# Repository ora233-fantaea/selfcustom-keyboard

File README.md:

# ESP32-S3 客制化键盘

一个基于 **Waveshare ESP32-S3-DEV-KIT-N16R8-M** 的 75% 客制化键盘工程，采用 **74HC165 级联移位寄存器**读键（非矩阵扫描），仅兼容 **Cherry MX 及兼容轴**。

> 状态：**原理图 + PCB 实质设计完成，尚未全布线**（属于可继续开发的骨架，非可投产图纸）。
> 更新日期：2026-11-23

## 特性

- **主控**：ESP32-S3-DEV-KIT-N16R8-M（16MB Flash / 8MB PSRAM），原生 USB HID。
- **读键方案**：10 片 74HC165 级联，每键独立输入 + 10kΩ 上拉，无矩阵、无二极管。
- **配列**：精确 75 键 / 6 行，方向键为标准**倒 T** 布局，Space 8.25u。
- **轴体**：75 个纯 MX 热插拔轴座（`SW_MX_HotSwap_PTH`）。
- **卫星轴**：plate-mount，4 个大键（Bksp / Enter / LShift / Space）。
- **定位板**：已建好，含键孔 / 卫星轴一体孔 / M3 孔 / 开发板避让窗，可发厂切割。
- **校验**：电气短路 **0**、走线交叉 **0**，原理图与 PCB 网络全部匹配。

## 目录结构

| 路径 | 说明 |
|---|---|
| [`kbd-esp32s3/`](kbd-esp32s3/) | KiCad 工程主体（原理图、PCB、定位板、生成脚本、预览图） |
| [`kbd-esp32s3/README.md`](kbd-esp32s3/README.md) | **工程详细文档**：电路、配列、元件、Pinout、网络、DRC、剩余边界 |
| [`ESP32-S3客制化键盘设计方案.md`](ESP32-S3客制化键盘设计方案.md) | 设计方案与选型（含主控选型、可行性结论） |
| [`ESP32-S3键盘方案_可行性验证报告.md`](ESP32-S3键盘方案_可行性验证报告.md) | 联网验证报告：GPIO / I2C / USB / PCB 设计规范 |

## 关键文件速览

- `kbd-esp32s3/kbd-esp32s3.kicad_sch` — 原理图（74HC165 级联读键）
- `kbd-esp32s3/kbd-esp32s3.kicad_pcb` — PCB（75 键 + 纯 MX 轴座 + 网络分配）
- `kbd-esp32s3/kbd-plate.dxf` — 定位板切割文件（发厂用）
- `kbd-esp32s3/pcb_preview.png` — PCB 2D 预览
- `kbd-esp32s3/render_keyboard.png` — 成品渲染图

完整的工程文件清单、电路说明、开发板 Pinout、卫星轴坐标和验证状态见 **[工程详细文档](kbd-esp32s3/README.md)**。

## 复现

工程文件由脚本生成，可在 `kbd-esp32s3/` 下重跑（需要 KiCad 9 的 `pcbnew` Python 模块）：

```bash
cd kbd-esp32s3
python3 gen_sch.py          # 原理图
python3 gen_pcb.py          # PCB（会覆盖 .kicad_pcb）
python3 gen_stabilizers.py  # 卫星轴开孔坐标表 + 示意图
python3 gen_plate.py        # 定位板 + DXF
python3 render_keyboard.py  # 成品渲染图
```

## 下一步

- 在 KiCad GUI 中完成 **397 条飞线**的布线（按键扫描线 / 电源 / 时钟 / 编码器 / USB）。
- 补副屏（SPI 长条屏）接口、外壳配合、实物焊接验证。
- 详情见 [工程详细文档 · 剩余边界](kbd-esp32s3/README.md#剩余边界下一步)。

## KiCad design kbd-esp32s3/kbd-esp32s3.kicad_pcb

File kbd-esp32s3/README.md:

# ESP32-S3 客制化键盘 · KiCad 工程

> 更新日期：2026-11-23
> 状态：**原理图 + PCB 实质设计**（非可投产图纸，布线未完成）
> 主控：Waveshare ESP32-S3-DEV-KIT-N16R8-M（16MB Flash / 8MB PSRAM）
> 轴体：**仅 Cherry MX 及兼容轴（已放弃 MX/Choc 混合兼容）**

## 工程文件

| 文件 | 说明 |
|---|---|
| `kbd-esp32s3.kicad_pro` | KiCad 9 工程文件 |
| `kbd-esp32s3.kicad_sch` | 原理图：74HC165 级联读键电路（非矩阵） |
| `kbd-esp32s3.kicad_pcb` | PCB：75 键真实配列 + 纯 MX 热插拔轴座 + 完整网络分配 |
| `gen_sch.py` / `lib_extract.py` | 原理图生成脚本（符号提取 + 布局 + 标签） |
| `gen_pcb.py` | PCB 生成脚本（pcbnew API，可重跑：配列/封装/网络/级联布线） |
| `gen_stabilizers.py` | 卫星轴定位板开孔数据生成（坐标表 + 示意图，可重跑） |
| `stabilizer_plate_holes.md` | 卫星轴开孔坐标表 + 采购清单 |
| `stabilizer_layout.png` | 卫星轴孔位示意图 |
| `gen_plate.py` | 定位板生成脚本（可重跑） |
| `kbd-plate.kicad_pcb` | 定位板板文件（Edge.Cuts：板框/键孔/卫星孔/M3/避让窗） |
| `kbd-plate.dxf` | 定位板切割文件（Edge.Cuts 层，发厂激光切割/CNC） |
| `plate_preview.png` | 定位板预览图 |

## 键盘输入电路（原理图和 PCB 一致）

**方案：74HC165 级联，每键独立输入，无矩阵、无二极管。**

- 10 片 74HC165，每片 8 路并行输入 = 80 路，覆盖 75 键，5 路空余接地。
- 每键：轴座 + 10kΩ 上拉电阻，独立接入一片 74HC165 的输入。
- 级联：前级 `Q7`(pin9) → 后级 `DS`(pin10)，网络 `CHAIN_1..CHAIN_9`；末片 `Q7` → `DATA`。
- 并行时钟 `CLK`(pin2)、锁存 `SH_LD`(pin1, 低有效) 全局并联；`~CE`(pin15) 接地常使能。
- 编码器：EC11 带按压，`ENC_A/ENC_B/ENC_SW` 独立引出，不进级联链。
- 接口：ESP32 开发板插座 = 两条独立 **1×22** 排母（P1/P2，2.54mm 间距），**两排中心距 21.80mm**；
  针数与中心距均按官方机械图 `ESP32-S3-DEV-KIT-N8R8_20260110` 与原理图 `Header 22` 标注核对，详见 `MODULE_CHECK.md`。
  板载 USB-C（J_USB）仅作原生 USB 数据备用，VBUS 不接。

## PCB 设计（本次完成）

### 配列：精确 75 键 / 6 行

| 行 | 键数 | 内容 |
|---|---|---|
| Row0 功能行 | 13 | Esc + F1~F12 |
| Row1 数字行 | 14 | ` 1-0 - = + Bksp(2u) |
| Row2 Q 行 | 14 | Tab(1.5u) Q-P [ ] \(1.5u) |
| Row3 A 行 | 13 | Caps(1.75u) A-L ; ' + Enter(2.25u) |
| Row4 Z 行 | 13 | LShift(2.25u) Z-M , . / + RShift(1.75u) + ↑ |
| Row5 底行 | 8 | LCtrl LWin LAlt + Space(8.25u) + Fn ← ↓ → |

- 键距 19.05mm，宽键按单位 u 计算，板框 **337.8 × 164.3mm**（重做后收紧：顶部窄带放开发板排针，74HC165 芯片带紧贴键区下方，消除了原底部约 60mm 空白）。
- **方向键采用标准倒 T 布局**：↑ 中心与 ↓ 对齐（x=14.5u），← ↓ → 三键并排在底行右侧，整簇紧凑、符合常规使用习惯。为腾出倒 T 所需空间，RShift 由 2.75u 缩至 1.75u、Space 由 6.25u 加长至 8.25u，总键数仍为 75。

### 元件

| 元件 | 数量 | 封装 / 说明 |
|---|---|---|
| 纯 MX 热插拔轴座 | 75 | `SW_MX_HotSwap_PTH`（仅 Cherry MX 及兼容轴，pad1=信号 / pad2=GND） |
| 上拉电阻 10k | 75 | 0603，pad1→VCC，pad2→按键网络 |
| 74HC165 | 10 | SOIC-16W，贴近对应键位组 |
| 去耦电容 100nF | 10 | 0603，每片 74HC165 一个 |
| ESP32 开发板插座 | 2 | 各 **1×22** 排母（P1/P2，2.54mm），水平放置，**中心距 21.80mm**，首针距板端 5.05/4.91mm；模块本体 63.30×25.40，四角 Ø2 安装孔（M1.4） |
| EC11 编码器 | 1 | 带按压开关 |
| USB-C | 1 | GCT USB4085（预留接口） |
| 安装孔 M3 | 4 | 四角 |

### 防共振开槽（Edge.Cuts 铣槽）

板面开槽用于打散整块 PCB 的弯曲共振、降低空腔音。**全部槽在 Edge.Cuts 层画闭合矩形**，74 个闭合轮廓（1 板框 + 73 槽）已验证全部闭合，KiCad/厂家按板内挖空（锣槽）处理。

- **大键减振槽**（5 处）：Space(8.25u) / Bksp(2u) / Enter(2.25u) / LShift(2.25u) / 底行右侧大键，在键中心上方 y=cy−8 开一条长槽（Space 槽长 152mm），打断大键下方整片板面的共振。槽宽 1.2mm。
- **键位隔离槽**（每键右上）：相邻键之间开竖槽，只开键的上半段（y 从 cy−6.5 到 cy−8），**下端留桥不贯穿**——MX 轴座焊盘集中在下半（y=+2.54/+5.08），槽避开焊盘区，同时保留机械连接不让板子散架。
- 槽位置经过 DRC 校验：`copper_edge_clearance` = **0**（不切焊盘/走线），短路 0、走线交叉 0。
- 可视化：`render_slots.py` 从 PCB 真实坐标生成 `pcb_slots_annotated.png`（红=槽）。

### 卫星轴（plate-mount，定位板卡扣）

**结论：卫星轴装在定位板上，PCB 无需开孔、无需改板。** 之前 PCB 未体现属正常，但定位板开孔坐标与 BOM 此前缺失，现已补齐（见 `gen_stabilizers.py` / `stabilizer_plate_holes.md` / `stabilizer_layout.png`）。

- 覆盖范围：**仅 2u 以上**（Bksp 2u / Enter 2.25u / LShift 2.25u / Space 8.25u），共 4 键 8 个 housing 位。
- 开孔：每个 housing 位约 6.65×12.3mm 矩形，中心坐标见 `stabilizer_plate_holes.md`（与 KiCad 板坐标一致）。
- 采购：2u plate-mount ×3、8u plate-mount ×1（2u/2.25u/2.75u 共用同一 2u 卫星轴）。
- **坑**：Space 是 8.25u，Cherry 无此档位；已按用户确认的 **8u（孔距 133.35mm，X=108.34/241.69）** 定死，下单键帽前仍须实测其卫星轴孔距。详见坐标表注意事项。

**定位板已建**（`gen_plate.py` 生成，**专为 MX 轴设计**）：整块 337.8×164.3mm（与重做后 PCB 一致），键孔 14×14（MX 标准）；2u/2.25u 大键的轴孔与卫星孔用 5mm 窄颈连通成一体开孔（plate-mount housing 必须这样才卡得进去），空格因卫星孔距中心 66.675mm 保持三孔独立。输出 `kbd-plate.kicad_pcb`（KiCad 可打开）与 `kbd-plate.dxf`（发厂切割）。避让窗 x[140,198] y[2,31] 供开发板排针。

### 开发板插座 Pinout（依据微雪官方原理图/尺寸图）

数据来源：[Waveshare ESP32-S3-DEV-KIT 文档](https://docs.waveshare.com/ESP32-S3-DEV-KIT-N8R8)、官方机械图包（PDF/DXF/STEP）、官方原理图。
实测标注：板体 63.30 × 25.40mm，2×22 排针 @2.54mm，两排中心距 21.80mm，排针距板边 1.80mm。
> 注：21.80mm 不是 2.54 的整数倍，因此该模块无法插入标准面包板——这是模块本身的特性。

| P1 (J_P1) | 网络 | P2 (J_P2) | 网络 |
|---|---|---|---|
| 1 | 3V3 → VCC | 1 | GND |
| 2 | EN → NC | 2 | TXD / GPIO43 |
| 3 | GPIO4 → **CLK** | 3 | RXD / GPIO44 |
| 4 | GPIO5 → **SH_LD** | 4 | GPIO1 |
| 5 | GPIO6 → **DATA** | 5 | GPIO2 |
| 6 | GPIO7 → **ENC_A** | 6 | GPIO42 |
| 7 | GPIO15 → **ENC_B** | 7 | GPIO41 |
| 8 | GPIO16 → **ENC_SW** | 8 | GPIO40 |
| 9 | GPIO17 | 9 | GPIO39 |
| 10 | GPIO18 | 10 | GPIO38 |
| 11 | GPIO8 | 11 | GPIO37 |
| 12 | GPIO3 | 12 | GPIO36 |
| 13 | GPIO46 | 13 | GPIO35 |
| 14 | GPIO9 | 14 | GPIO0 (BOOT) |
| 15 | GPIO10 | 15 | GPIO45 |
| 16 | GPIO11 | 16 | GPIO48 |
| 17 | GPIO12 | 17 | GPIO47 |
| 18 | GPIO13 | 18 | GPIO21 |
| 19 | GPIO14 | 19 | GPIO20 (USB D+) |
| 20 | 5V → NC | 20 | GPIO19 (USB D-) |

> 注：本项目需要的 6 个信号（CLK/SH_LD/DATA/ENC_A/B/SW）已映射到 P1 的 GPIO4/5/6/7/15/16；其余 GPIO 针脚按官方定义保留网络名备用。NC 引脚为板子上未连接/NC 的 GPIO（如 GPIO35/36/37 在 WROOM-1 上不引出）。

### 网络分配

- 129 个网络：K01~K75（按键）、CHAIN_1~10（级联，末片 CHAIN_10 即 ESP32 DATA）、CLK、SH_LD、ENC_A/B/SW、GPIO1~48（开发板插座备用针脚）、VCC、GND、VBUS、USB_D±、CC1/CC2。
- 原理图 92 个网络与 PCB **全部匹配**（已脚本核对），GUI 中 F8 同步不会报网络错误。
- **所有焊盘已分配网络**（网络名即飞线依据）。
- 已预布最关键的**级联数据链**：Q7/DS 为 SOIC 相邻引脚，同层无法避开交叉，故级联改走 **B.Cu 背面独立通道**（出口列打过孔下到背面），正面所有引线零交叉。

## 验证状态

| 检查项 | 结果 |
|---|---|
| 原理图加载 / ERC 电气错误 | ✅ 通过 / 0 error |
| PCB 加载 / 导出 SVG | ✅ 通过 |
| DRC 电气短路（shorting_items） | ✅ **0 个** |
| DRC 未连接项 | 397（预期：按键扫描线/电源/时钟/地尚未布线） |
| 其余 DRC 警告 | 240 项非电气警告：courtyard_overlap 75 + hole_clearance 151（轴座 PTH 孔密集的固有特性）+ clearance 14（USB-C 密脚封装固有 0.15mm 间隙）。短路 0、走线交叉 0。 |

## 剩余边界（下一步）

1. **布线未完成**：397 个飞线需在 KiCad GUI 中完成（自动布线器或手动）——按键扫描线、上拉电阻 VCC、74HC165 电源/时钟/锁存、编码器、USB。级联数据链已预布（走 B.Cu）。
2. **网表同步**：本 PCB 的网络分配由脚本直接写入，与原理图网络名一致；GUI 打开后可执行 F8 核对。
3. **ERC 10 个 `lib_symbol_mismatch`**：74HC165 继承符号展开的缓存差异，"更新符号库缓存"可消除，非电气问题。
4. **DRC 布局警告**：240 项均为机械/密脚警告（轴座 PTH 孔间距、USB-C 密脚），非短路非交叉；可后续调整孔间距规则清理，不影响电气。
5. **尚未做**：副屏（SPI 长条屏）接口、真实外壳/定位板配合、MX 轴座的实物焊接验证。级联链已改走 B.Cu 背面独立通道，消除了 F.Cu 相邻引脚跨接交叉。
6. **定位板**：已建好（`kbd-plate.kicad_pcb` + `kbd-plate.dxf`），板框 337.8×164.3mm、与 PCB 对齐；含 75 个 14×14 键孔、8 个卫星轴孔（2u 级与中心轴孔用窄颈连通为一体孔，空格三孔独立）、4×M3 Ø3.2、顶部开发板避让窗。建议 1.5mm FR4 或铝板，发厂用 `kbd-plate.dxf`。PCB 无需改动。

## 环境说明

- KiCad 9.0.9（官方 PPA）；headless 环境，用 `kicad-cli` 和 `pcbnew` Python API 操作。
- 第三方键盘封装库：`/root/.local/share/kicad/9.0/footprints/`。
- 全局库表 `sym-lib-table` / `fp-lib-table` 已配置在 `~/.config/kicad/9.0/`。
- 重跑生成：`python3 gen_pcb.py`（会覆盖 .kicad_pcb）。

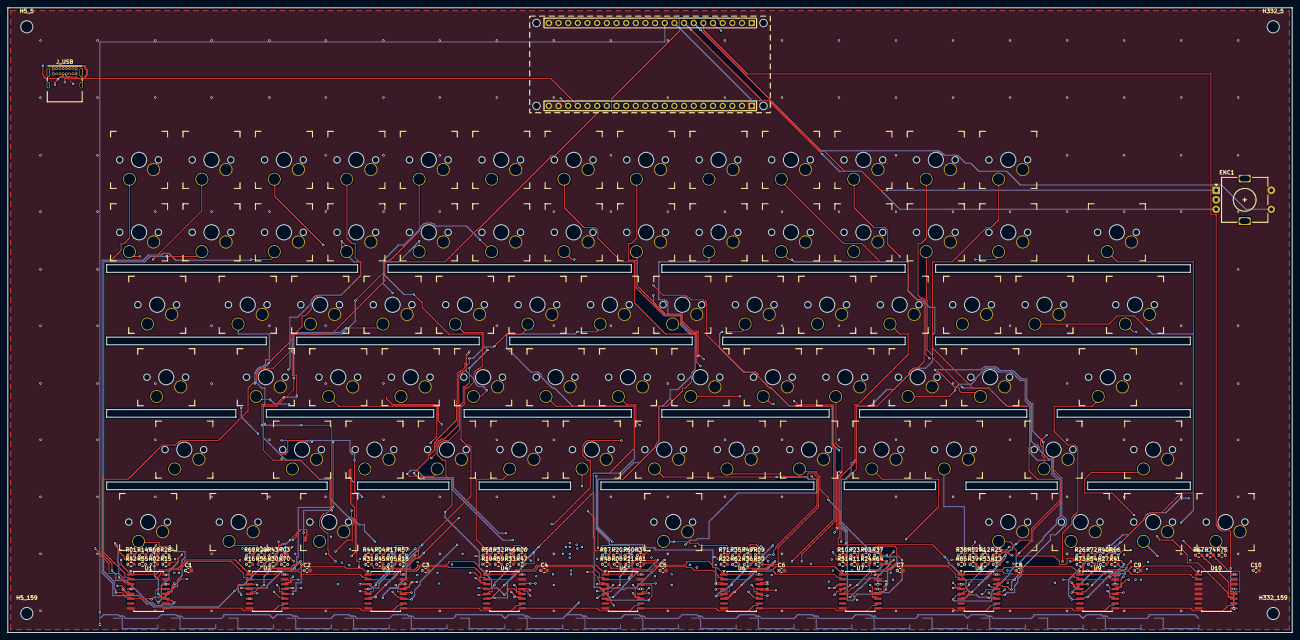
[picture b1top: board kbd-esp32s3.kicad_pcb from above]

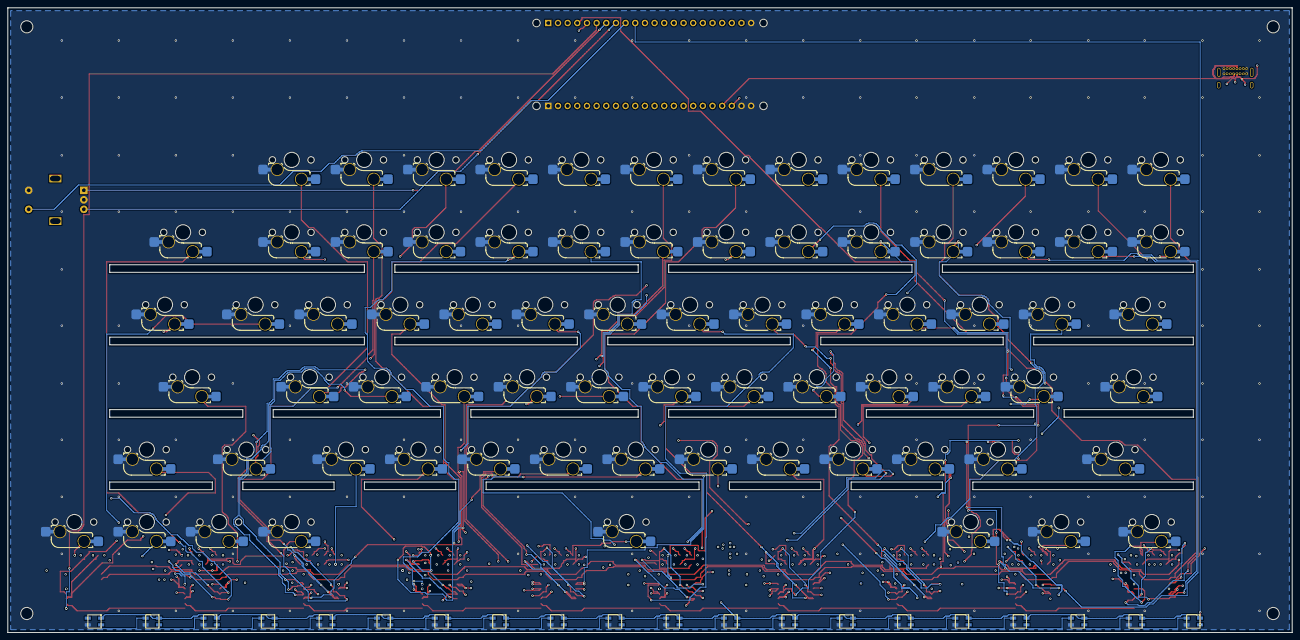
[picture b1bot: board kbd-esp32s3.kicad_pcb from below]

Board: 4 copper layers, 337.8 x 164.3 mm, 199 parts (20 on the bottom side), 115 nets.

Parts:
C1, C2, C3, C4, C5, C6, C7, C8, C9, C10: 100nF; C_0603_1608Metric
ENC1: EC11; RotaryEncoder_Alps_EC11E-Switch_Vertical_H20mm
H5_5, H5_159, H332_5, H332_159: M3; MountingHole_3.2mm_M3
J_P1: DEV-KIT-P1; PinHeader_1x22_P2.54mm_Vertical
J_P2: DEV-KIT-P2; PinHeader_1x22_P2.54mm_Vertical
J_USB: USB-C(数据备用); USB_C_Receptacle_GCT_USB4085
L01, L02, L03, L04, L05, L06, L07, L08, L09, L10, L11, L12, L13, L14, L15, L16, L17, L18, L19, L20: SK6812MINI-E; LED_SK6812MINI-E
MOD1: ESP32-S3-DEV-KIT-N16R8-M; Waveshare_ESP32-S3-DEV-KIT-N16R8-M
R01, R02, R03, R04, R05, R06, R07, R08, R09, R10, R11, R12, R13, R14, R15, R16, R17, R18, R19, R20, R21, R22, R23, R24, R25, R26, R27, R28, R29, R30, R31, R32, R33, R34, R35, R36, R37, R38, R39, R40, R41, R42, R43, R44, R45, R46, R47, R48, R49, R50, R51, R52, R53, R54, R55, R56, R57, R58, R59, R60, R61, R62, R63, R64, R65, R66, R67, R68, R69, R70, R71, R72, R73, R74, R75: 10k; R_0603_1608Metric
SW01: Esc; SW_MX_HotSwap_PTH
SW02: F1; SW_MX_HotSwap_PTH
SW03: F2; SW_MX_HotSwap_PTH
SW04: F3; SW_MX_HotSwap_PTH
SW05: F4; SW_MX_HotSwap_PTH
SW06: F5; SW_MX_HotSwap_PTH
SW07: F6; SW_MX_HotSwap_PTH
SW08: F7; SW_MX_HotSwap_PTH
SW09: F8; SW_MX_HotSwap_PTH
SW10: F9; SW_MX_HotSwap_PTH
SW11: F10; SW_MX_HotSwap_PTH
SW12: F11; SW_MX_HotSwap_PTH
SW13: F12; SW_MX_HotSwap_PTH
SW14: `; SW_MX_HotSwap_PTH
SW15: 1; SW_MX_HotSwap_PTH
SW16: 2; SW_MX_HotSwap_PTH
SW17: 3; SW_MX_HotSwap_PTH
SW18: 4; SW_MX_HotSwap_PTH
SW19: 5; SW_MX_HotSwap_PTH
SW20: 6; SW_MX_HotSwap_PTH
SW21: 7; SW_MX_HotSwap_PTH
SW22: 8; SW_MX_HotSwap_PTH
SW23: 9; SW_MX_HotSwap_PTH
SW24: 0; SW_MX_HotSwap_PTH
SW25: -; SW_MX_HotSwap_PTH
SW26: =; SW_MX_HotSwap_PTH
SW27: Bksp; SW_MX_HotSwap_PTH
SW28: Tab; SW_MX_HotSwap_PTH
SW29: Q; SW_MX_HotSwap_PTH
SW30: W; SW_MX_HotSwap_PTH
SW31: E; SW_MX_HotSwap_PTH
SW32: R; SW_MX_HotSwap_PTH
SW33: T; SW_MX_HotSwap_PTH
SW34: Y; SW_MX_HotSwap_PTH
SW35: U; SW_MX_HotSwap_PTH
SW36: I; SW_MX_HotSwap_PTH
SW37: O; SW_MX_HotSwap_PTH
SW38: P; SW_MX_HotSwap_PTH
SW39: [; SW_MX_HotSwap_PTH
SW40: ]; SW_MX_HotSwap_PTH
SW41: \\\\\\\\\\\\\\\\\\\\\\\\\\\\\\\\\\\\\\\\\\\\\\\\\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; SW_MX_HotSwap_PTH
SW42: Caps; SW_MX_HotSwap_PTH
SW43: A; SW_MX_HotSwap_PTH
SW44: S; SW_MX_HotSwap_PTH
SW45: D; SW_MX_HotSwap_PTH
SW46: F; SW_MX_HotSwap_PTH
SW47: G; SW_MX_HotSwap_PTH
SW48: H; SW_MX_HotSwap_PTH
SW49: J; SW_MX_HotSwap_PTH
SW50: K; SW_MX_HotSwap_PTH
SW51: L; SW_MX_HotSwap_PTH
SW52: ;; SW_MX_HotSwap_PTH
SW53: '; SW_MX_HotSwap_PTH
SW54: Enter; SW_MX_HotSwap_PTH
SW55: LShift; SW_MX_HotSwap_PTH
SW56: Z; SW_MX_HotSwap_PTH
SW57: X; SW_MX_HotSwap_PTH
SW58: C; SW_MX_HotSwap_PTH
SW59: V; SW_MX_HotSwap_PTH
SW60: B; SW_MX_HotSwap_PTH
SW61: N; SW_MX_HotSwap_PTH
SW62: M; SW_MX_HotSwap_PTH
SW63: ,; SW_MX_HotSwap_PTH
SW64: .; SW_MX_HotSwap_PTH
SW65: /; SW_MX_HotSwap_PTH
SW66: RShift; SW_MX_HotSwap_PTH
SW67: Up; SW_MX_HotSwap_PTH
SW68: LCtrl; SW_MX_HotSwap_PTH
SW69: LWin; SW_MX_HotSwap_PTH
SW70: LAlt; SW_MX_HotSwap_PTH
SW71: Space; SW_MX_HotSwap_PTH
SW72: Fn; SW_MX_HotSwap_PTH
SW73: Left; SW_MX_HotSwap_PTH
SW74: Down; SW_MX_HotSwap_PTH
SW75: Right; SW_MX_HotSwap_PTH
U1, U2, U3, U4, U5, U6, U7, U8, U9, U10: 74HC165; SOIC-16W_7.5x10.3mm_P1.27mm

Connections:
CHAIN_1: U1.9, U2.10
CHAIN_2: U2.9, U3.10
CHAIN_3: U3.9, U4.10
CHAIN_4: U4.9, U5.10
CHAIN_5: U5.9, U6.10
CHAIN_6: U6.9, U7.10
CHAIN_7: U7.9, U8.10
CHAIN_8: U8.9, U9.10
CHAIN_9: U9.9, U10.10
CHAIN_10: J_P1.6, U10.9
CLK: J_P1.4, U1.2, U2.2, U3.2, U4.2, U5.2, U6.2, U7.2, U8.2, U9.2, U10.2
ENC_A: ENC1.A, J_P1.7
ENC_B: ENC1.B, J_P1.8
ENC_SW: ENC1.S1, J_P1.9
GND: C1.2, C2.2, C3.2, C4.2, C5.2, C6.2, C7.2, C8.2, C9.2, C10.2, ENC1.C, ENC1.S2, J_P1.22, J_P2.1, J_P2.21, J_P2.22, J_USB.A1, J_USB.A12, J_USB.B1, J_USB.B12, L01.3, L02.3, L03.3, L04.3, L05.3, L06.3, L07.3, L08.3, L09.3, L10.3, L11.3, L12.3, L13.3, L14.3, L15.3, L16.3, L17.3, L18.3, L19.3, L20.3, SW01.2, SW02.2, SW03.2, SW04.2, SW05.2, SW06.2, SW07.2, SW08.2, SW09.2, SW10.2, SW11.2, SW12.2, SW13.2, SW14.2, SW15.2, SW16.2, SW17.2, SW18.2, SW19.2, SW20.2, SW21.2, SW22.2, SW23.2, SW24.2, SW25.2, SW26.2, SW27.2, SW28.2, SW29.2, SW30.2, SW31.2, SW32.2, SW33.2, SW34.2, SW35.2, SW36.2, SW37.2, SW38.2, SW39.2, SW40.2, SW41.2, SW42.2, SW43.2, SW44.2, SW45.2, SW46.2, SW47.2, SW48.2, SW49.2, SW50.2, SW51.2, SW52.2, SW53.2, SW54.2, SW55.2, SW56.2, SW57.2, SW58.2, SW59.2, SW60.2, SW61.2, SW62.2, SW63.2, SW64.2, SW65.2, SW66.2, SW67.2, SW68.2, SW69.2, SW70.2, SW71.2, SW72.2, SW73.2, SW74.2, SW75.2, U1.8, U1.10, U1.15, U2.8, U2.15, U3.8, U3.15, U4.8, U4.15, U5.8, U5.15, U6.8, U6.15, U7.8, U7.15, U8.8, U8.15, U9.8, U9.15, U10.3, U10.4, U10.5, U10.6, U10.8, U10.14, U10.15
K01: R01.2, SW01.1, U1.11
K02: R02.2, SW02.1, U1.5
K03: R03.2, SW03.1, U2.14
K04: R04.2, SW04.1, U3.12
K05: R05.2, SW05.1, U3.5
K06: R06.2, SW06.1, U4.14
K07: R07.2, SW07.1, U5.11
K08: R08.2, SW08.1, U5.4
K09: R09.2, SW09.1, U6.14
K10: R10.2, SW10.1, U7.11
K11: R11.2, SW11.1, U7.4
K12: R12.2, SW12.1, U8.13
K13: R13.2, SW13.1, U8.6
K14: R14.2, SW14.1, U1.12
K15: R15.2, SW15.1, U1.6
K16: R16.2, SW16.1, U2.3
K17: R17.2, SW17.1, U3.13
K18: R18.2, SW18.1, U3.6
K19: R19.2, SW19.1, U4.3
K20: R20.2, SW20.1, U5.12
K21: R21.2, SW21.1, U5.5
K22: R22.2, SW22.1, U6.3
K23: R23.2, SW23.1, U7.12
K24: R24.2, SW24.1, U7.5
K25: R25.2, SW25.1, U8.14
K26: R26.2, SW26.1, U9.11
K27: R27.2, SW27.1, U9.5
K28: R28.2, SW28.1, U1.14
K29: R29.2, SW29.1, U2.12
K30: R30.2, SW30.1, U2.5
K31: R31.2, SW31.1, U3.3
K32: R32.2, SW32.1, U4.12
K33: R33.2, SW33.1, U4.5
K34: R34.2, SW34.1, U5.14
K35: R35.2, SW35.1, U6.12
K36: R36.2, SW36.1, U6.5
K37: R37.2, SW37.1, U7.14
K38: R38.2, SW38.1, U8.11
K39: R39.2, SW39.1, U8.4
K40: R40.2, SW40.1, U9.13
K41: R41.2, SW41.1, U9.6
K42: R42.2, SW42.1, U1.3
K43: R43.2, SW43.1, U2.13
K44: R44.2, SW44.1, U3.11
K45: R45.2, SW45.1, U3.4
K46: R46.2, SW46.1, U4.13
K47: R47.2, SW47.1, U4.6
K48: R48.2, SW48.1, U5.3
K49: R49.2, SW49.1, U6.13
K50: R50.2, SW50.1, U6.6
K51: R51.2, SW51.1, U7.3
K52: R52.2, SW52.1, U8.12
K53: R53.2, SW53.1, U8.5
K54: R54.2, SW54.1, U9.4
K55: R55.2, SW55.1, U1.4
K56: R56.2, SW56.1, U2.4
K57: R57.2, SW57.1, U3.14
K58: R58.2, SW58.1, U4.11
K59: R59.2, SW59.1, U4.4
K60: R60.2, SW60.1, U5.13
K61: R61.2, SW61.1, U5.6
K62: R62.2, SW62.1, U6.4
K63: R63.2, SW63.1, U7.13
K64: R64.2, SW64.1, U7.6
K65: R65.2, SW65.1, U8.3
K66: R66.2, SW66.1, U9.14
K67: R67.2, SW67.1, U10.11
K68: R68.2, SW68.1, U1.13
K69: R69.2, SW69.1, U2.11
K70: R70.2, SW70.1, U2.6
K71: R71.2, SW71.1, U6.11
K72: R72.2, SW72.1, U9.12
K73: R73.2, SW73.1, U9.3
K74: R74.2, SW74.1, U10.12
K75: R75.2, SW75.1, U10.13
LED_D0: L01.2, L02.4
LED_D1: L02.2, L03.4
LED_D2: L03.2, L04.4
LED_D3: L04.2, L05.4
LED_D4: L05.2, L06.4
LED_D5: L06.2, L07.4
LED_D6: L07.2, L08.4
LED_D7: L08.2, L09.4
LED_D8: L09.2, L10.4
LED_D9: L10.2, L11.4
LED_D10: L11.2, L12.4
LED_D11: L12.2, L13.4
LED_D12: L13.2, L14.4
LED_D13: L14.2, L15.4
LED_D14: L15.2, L16.4
LED_D15: L16.2, L17.4
LED_D16: L17.2, L18.4
LED_D17: L18.2, L19.4
LED_D18: L19.2, L20.4
LED_DATA: J_P1.10, L01.4
SH_LD: J_P1.5, U1.1, U2.1, U3.1, U4.1, U5.1, U6.1, U7.1, U8.1, U9.1, U10.1
USB_D+: J_P2.19, J_USB.A6, J_USB.B6
USB_D-: J_P2.20, J_USB.A7, J_USB.B7
V5: J_P1.21, L01.1, L02.1, L03.1, L04.1, L05.1, L06.1, L07.1, L08.1, L09.1, L10.1, L11.1, L12.1, L13.1, L14.1, L15.1, L16.1, L17.1, L18.1, L19.1, L20.1
VCC: C1.1, C2.1, C3.1, C4.1, C5.1, C6.1, C7.1, C8.1, C9.1, C10.1, J_P1.1, J_P1.2, R01.1, R02.1, R03.1, R04.1, R05.1, R06.1, R07.1, R08.1, R09.1, R10.1, R11.1, R12.1, R13.1, R14.1, R15.1, R16.1, R17.1, R18.1, R19.1, R20.1, R21.1, R22.1, R23.1, R24.1, R25.1, R26.1, R27.1, R28.1, R29.1, R30.1, R31.1, R32.1, R33.1, R34.1, R35.1, R36.1, R37.1, R38.1, R39.1, R40.1, R41.1, R42.1, R43.1, R44.1, R45.1, R46.1, R47.1, R48.1, R49.1, R50.1, R51.1, R52.1, R53.1, R54.1, R55.1, R56.1, R57.1, R58.1, R59.1, R60.1, R61.1, R62.1, R63.1, R64.1, R65.1, R66.1, R67.1, R68.1, R69.1, R70.1, R71.1, R72.1, R73.1, R74.1, R75.1, U1.16, U2.16, U3.16, U4.16, U5.16, U6.16, U7.16, U8.16, U9.16, U10.16

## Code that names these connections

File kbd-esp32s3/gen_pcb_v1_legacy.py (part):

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             nets=p2_nets, rot=90)

# 项目信号 -> 开发板 GPIO（用标签网络名保持一致，便于飞线）
# CLK->GPIO4(P1.3), SH_LD->GPIO5(P1.4), CHAIN_10(DATA)->GPIO6(P1.5)
# ENC_A->GPIO7(P1.6), ENC_B->GPIO15(P1.7), ENC_SW->GPIO16(P1.8)
# 覆盖为项目网络名（覆盖上面占位 GPIO 名）
for padnum, net in {"3":"CLK", "4":"SH_LD", "5":"CHAIN_10",
                    "6":"ENC_A", "7":"ENC_B", "8":"ENC_SW"}.items():
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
